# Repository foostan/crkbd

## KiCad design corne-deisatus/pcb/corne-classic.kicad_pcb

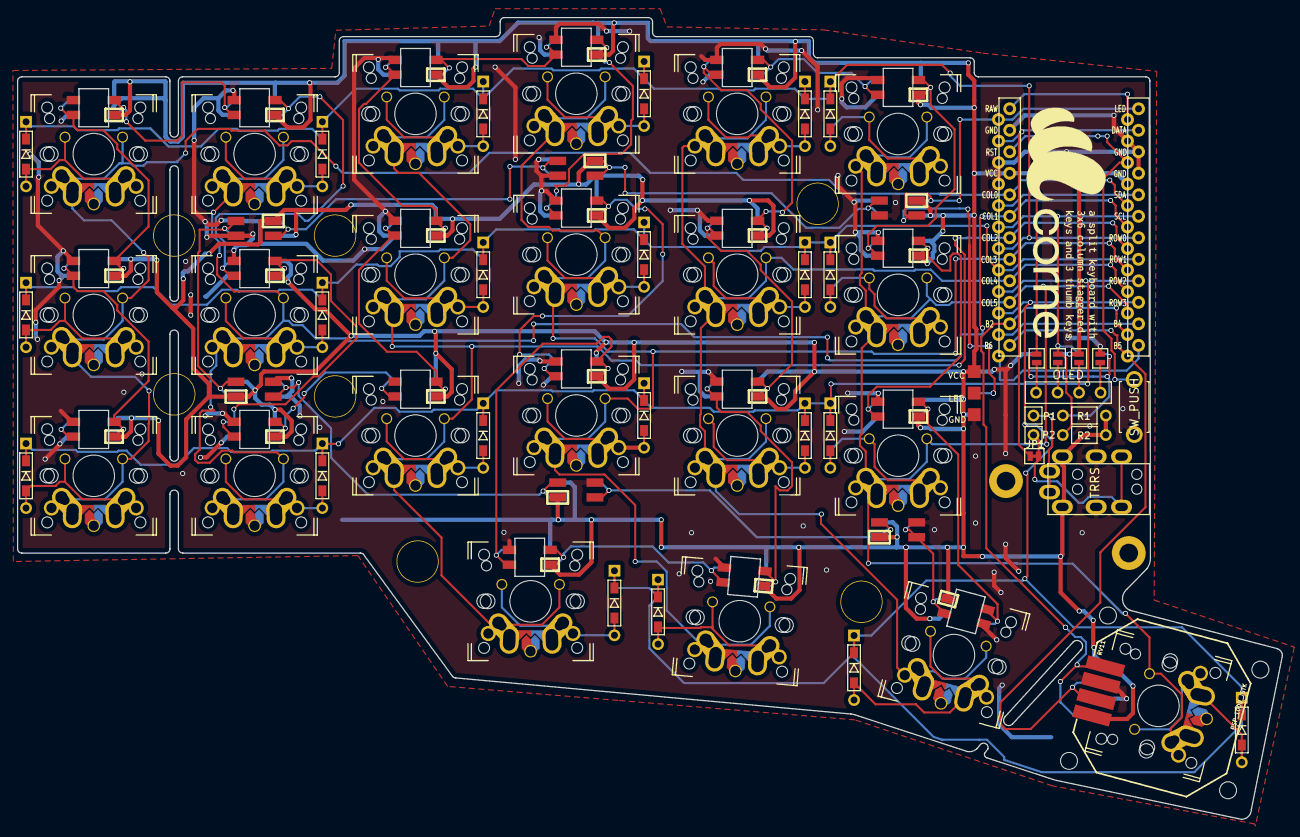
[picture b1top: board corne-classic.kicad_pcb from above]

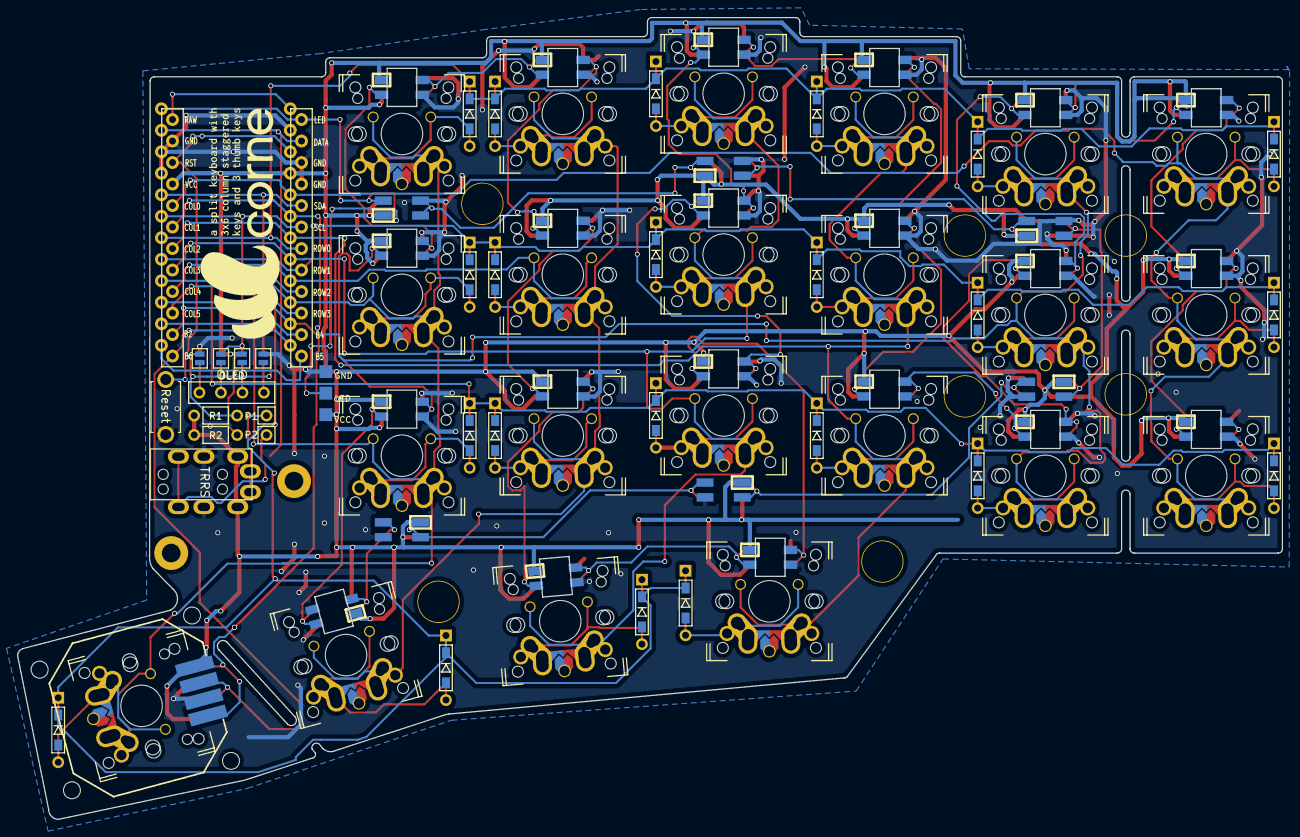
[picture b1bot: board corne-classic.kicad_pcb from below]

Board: 2 copper layers, 149.4 x 94.7 mm, 90 parts (4 on the bottom side), 73 nets.

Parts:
D1, D2, D3, D4, D5, D6, D7, D8, D9, D10, D11, D12, D13, D14, D15, D16, D17, D18, D19, D20, D21, D22: D; D3_TH_SMD
J1: MJ-4PP-9
J2: OLED
J3: LED; StripLED_rev
JP1: JP
JP2, JP3, JP4, JP5, JP6, JP7, JP8, JP9: Jumper
L1, L2, L3, L4, L5, L6: SK6812MINI; SK6812MINI_underglow_rev
L7, L8, L9, L10, L11, L12, L13, L14, L15, L16, L17, L18, L19, L20, L21, L22, L23, L24, L25, L26, L27: SK6812MINI; SK6812MINI_rev
P1, P2: i2c-pin; 1pin_conn
R1, R2: R
RSW1: SW_PUSH; ResetSW
RV11: PSP_1000_JSTK; JOYSTICK-PSP1000-reverse
SW1, SW2, SW3, SW4, SW5, SW6, SW7, SW8, SW9, SW10, SW11, SW12, SW13, SW14, SW15, SW16, SW17, SW18, SW19, SW22: SW_PUSH; MX-ALPS-Choc-X-straight-crane2
SW20, SW21: SW_PUSH; MX-ALPS-Choc-X-straight-crane2-u1.5
U1: ProMicro; ProMicro_v2

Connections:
GND: J1.C, J3.1, JP2.1, JP9.1, L1.2, L2.2, L3.2, L4.2, L5.2, L6.2, L7.2, L8.2, L9.2, L10.2, L11.2, L12.2, L13.2, L14.2, L15.2, L16.2, L17.2, L18.2, L19.2, L20.2, L21.2, L22.2, L23.2, L24.2, L25.2, L26.2, L27.2, RSW1.2, RV11.2, U1.3, U1.4, U1.23
LED: J3.2, L3.3, U1.1
unnamed: D1.2, SW1.2
unnamed: D2.2, SW2.2
unnamed: D3.2, SW3.2
unnamed: D4.2, SW4.2
unnamed: D5.2, SW5.2
unnamed: D6.2, SW6.2
unnamed: D7.2, SW7.2
unnamed: D8.2, SW8.2
unnamed: D9.2, SW9.2
unnamed: D10.2, SW10.2
unnamed: D11.2, SW11.2
unnamed: D12.2, SW12.2
unnamed: D13.2, SW13.2
unnamed: D14.2, SW14.2
unnamed: D15.2, SW15.2
unnamed: D16.2, SW16.2
unnamed: D17.2, SW17.2
unnamed: D18.2, SW18.2
unnamed: D19.2, SW20.2
unnamed: D20.2, SW21.2
unnamed: D21.2, SW22.2
unnamed: D22.2, SW19.2
unnamed: J1.A, P1.1
unnamed: J1.B, JP1.2, P2.1
unnamed: J2.1, JP5.2, JP9.2
unnamed: J2.2, JP4.2, JP8.2
unnamed: J2.3, JP3.2, JP7.2
unnamed: J2.4, JP2.2, JP6.2
unnamed: L1.1, L4.3
unnamed: L1.3, L2.1
unnamed: L2.3, L3.1
unnamed: L4.1, L5.3
unnamed: L5.1, L6.3
unnamed: L7.3, L8.1
unnamed: L9.3, L10.1
unnamed: L10.3, L16.1
unnamed: L11.1, L17.3
unnamed: L11.3, L12.1
unnamed: L12.3, L18.1
unnamed: L13.1, L19.3
unnamed: L7.1, L13.3
unnamed: L8.3, L14.1
unnamed: L14.3, L20.1
unnamed: L15.1, L21.3
unnamed: L9.1, L15.3
unnamed: L16.3, L22.1
unnamed: L17.1, L23.3
unnamed: L18.3, L24.1
unnamed: L20.3, L21.1
unnamed: L22.3, L25.1
unnamed: L23.1, L26.3
unnamed: L24.3, L27.1
unnamed: L25.3, L26.1
unnamed: L6.1, L27.3
SCL: JP4.1, JP7.1, R2.2, U1.6
SDA: JP5.1, JP6.1, R1.2, U1.5
VCC: J1.D, J3.3, JP3.1, JP8.1, L1.4, L2.4, L3.4, L4.4, L5.4, L6.4, L7.4, L8.4, L9.4, L10.4, L11.4, L12.4, L13.4, L14.4, L15.4, L16.4, L17.4, L18.4, L19.4, L20.4, L21.4, L22.4, L23.4, L24.4, L25.4, L26.4, L27.4, R1.1, R2.1, RV11.4, U1.21
analogX: RV11.1, U1.14
analogY: RV11.3, U1.13
col0: SW1.1, SW7.1, SW13.1, U1.20
col1: SW2.1, SW8.1, SW14.1, U1.19
col2: SW3.1, SW9.1, SW15.1, SW19.1, U1.18
col3: SW4.1, SW10.1, SW16.1, SW20.1, U1.17
col4: SW5.1, SW11.1, SW17.1, SW21.1, U1.16
col5: SW6.1, SW12.1, SW18.1, SW22.1, U1.15
data: JP1.1, U1.2
reset: RSW1.1, U1.22
row0: D1.1, D2.1, D3.1, D4.1, D5.1, D6.1, U1.7
row1: D7.1, D8.1, D9.1, D10.1, D11.1, D12.1, U1.8
row2: D13.1, D14.1, D15.1, D16.1, D17.1, D18.1, U1.9
row3: D19.1, D20.1, D21.1, D22.1, U1.10

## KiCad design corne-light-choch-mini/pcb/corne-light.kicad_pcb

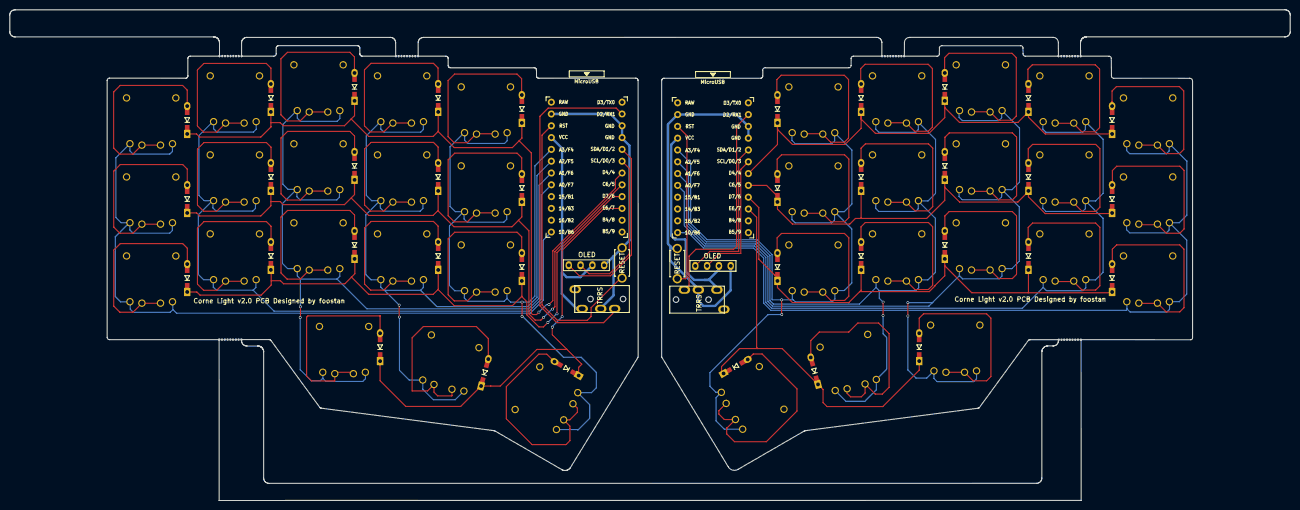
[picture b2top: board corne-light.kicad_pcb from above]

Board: 2 copper layers, 275.5 x 105.6 mm, 80 parts (0 on the bottom side), 66 nets.

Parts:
D2, D3, D4, D5, D6, D8, D9, D10, D11, D12, D14, D15, D16, D17, D18, D19, D20, D21, D23, D24, D25, D26, D27, D29, D30, D31, D32, D33, D35, D36, D37, D38, D39, D40, D41, D42: D; D3_TH
J1, J6: MJ-4PP-9; MJ-4PP-9_1side
J2, J7: OLED; OLED_1side
RSW1, RSW2: SW_PUSH; ResetSW_1side
SW2, SW3, SW4, SW5, SW6, SW8, SW9, SW10, SW11, SW12, SW14, SW15, SW16, SW17, SW18, SW19, SW20, SW21, SW23, SW24, SW25, SW26, SW27, SW29, SW30, SW31, SW32, SW33, SW35, SW36, SW37, SW38, SW39, SW40, SW41, SW42: SW_PUSH; Kailh_PG1232
U1, U2: ProMicro; ProMicro_v3

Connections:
GND: J1.C, J2.4, RSW1.2, U1.3 (GND), U1.4 (GND), U1.23 (GND)
GNDA: J6.C, J7.4, RSW2.2, U2.3 (GND), U2.4 (GND), U2.23 (GND)
unnamed: D2.2 (A), SW2.2
unnamed: D3.2 (A), SW3.2
unnamed: D4.2 (A), SW4.2
unnamed: D5.2 (A), SW5.2
unnamed: D6.2 (A), SW6.2
unnamed: D8.2 (A), SW8.2
unnamed: D9.2 (A), SW9.2
unnamed: D10.2 (A), SW10.2
unnamed: D11.2 (A), SW11.2
unnamed: D12.2 (A), SW12.2
unnamed: D14.2 (A), SW14.2
unnamed: D15.2 (A), SW15.2
unnamed: D16.2 (A), SW16.2
unnamed: D17.2 (A), SW17.2
unnamed: D18.2 (A), SW18.2
unnamed: D19.2 (A), SW19.2
unnamed: D20.2 (A), SW20.2
unnamed: D21.2 (A), SW21.2
unnamed: D23.2 (A), SW23.2
unnamed: D24.2 (A), SW24.2
unnamed: D25.2 (A), SW25.2
unnamed: D26.2 (A), SW26.2
unnamed: D27.2 (A), SW27.2
unnamed: D29.2 (A), SW29.2
unnamed: D30.2 (A), SW30.2
unnamed: D31.2 (A), SW31.2
unnamed: D32.2 (A), SW32.2
unnamed: D33.2 (A), SW33.2
unnamed: D35.2 (A), SW35.2
unnamed: D36.2 (A), SW36.2
unnamed: D37.2 (A), SW37.2
unnamed: D38.2 (A), SW38.2
unnamed: D39.2 (A), SW39.2
unnamed: D40.2 (A), SW40.2
unnamed: D41.2 (A), SW41.2
unnamed: D42.2 (A), SW42.2
SCL: J2.2, U1.6 (3/D0/SCL)
SCL_r: J7.2, U2.6 (3/D0/SCL)
SDA: J2.1, U1.5 (2/D1/SDA)
SDA_r: J7.1, U2.5 (2/D1/SDA)
VCC: J1.D, J2.3, U1.21 (VCC)
VDD: J6.D, J7.3, U2.21 (VCC)
col1: SW2.1, SW8.1, SW14.1, U1.13 (B6/10)
col1_r: SW23.1, SW29.1, SW35.1, U2.13 (B6/10)
col2: SW3.1, SW9.1, SW15.1, U1.17 (F7/A0)
col2_r: SW24.1, SW30.1, SW36.1, U2.17 (F7/A0)
col3: SW4.1, SW10.1, SW16.1, SW19.1, U1.18 (F6/A1)
col3_r: SW25.1, SW31.1, SW37.1, SW40.1, U2.18 (F6/A1)
col4: SW5.1, SW11.1, SW17.1, SW20.1, U1.19 (F5/A2)
col4_r: SW26.1, SW32.1, SW38.1, SW41.1, U2.19 (F5/A2)
col5: SW6.1, SW12.1, SW18.1, SW21.1, U1.20 (F4/A3)
col5_r: SW27.1, SW33.1, SW39.1, SW42.1, U2.20 (F4/A3)
data: J1.B, U1.2 (RX1/D2)
data_r: J6.B, U2.2 (RX1/D2)
reset: RSW1.1, U1.22 (RST)
reset_r: RSW2.1, U2.22 (RST)
row0: D2.1 (K), D3.1 (K), D4.1 (K), D5.1 (K), D6.1 (K), U1.7 (4/D4)
row0_r: D23.1 (K), D24.1 (K), D25.1 (K), D26.1 (K), D27.1 (K), U2.7 (4/D4)
row1: D8.1 (K), D9.1 (K), D10.1 (K), D11.1 (K), D12.1 (K), U1.8 (5/C6)
row1_r: D29.1 (K), D30.1 (K), D31.1 (K), D32.1 (K), D33.1 (K), U2.8 (5/C6)
row2: D14.1 (K), D15.1 (K), D16.1 (K), D17.1 (K), D18.1 (K), U1.9 (6/D7)
row2_r: D35.1 (K), D36.1 (K), D37.1 (K), D38.1 (K), D39.1 (K), U2.9 (6/D7)
row3: D19.1 (K), D20.1 (K), D21.1 (K), U1.10 (7/E6)
row3_r: D40.1 (K), D41.1 (K), D42.1 (K), U2.10 (7/E6)

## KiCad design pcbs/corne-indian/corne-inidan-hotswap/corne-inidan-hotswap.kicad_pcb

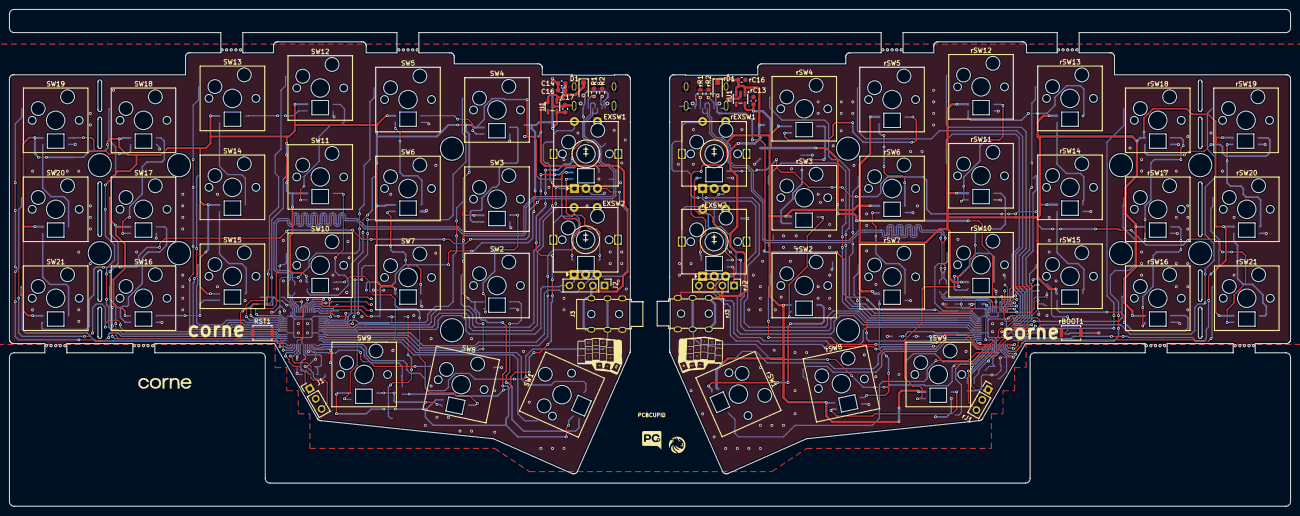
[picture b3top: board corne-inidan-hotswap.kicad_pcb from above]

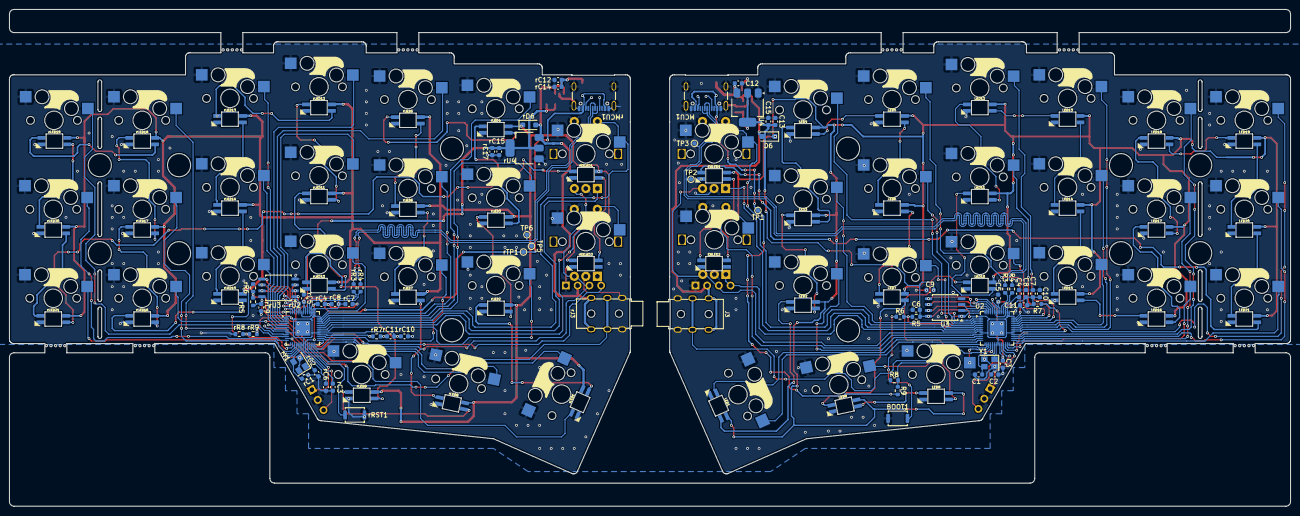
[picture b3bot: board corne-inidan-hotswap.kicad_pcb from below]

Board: 2 copper layers, 277.2 x 107.5 mm, 176 parts (109 on the bottom side), 151 nets.

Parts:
BOOT1: SKRKAGE020; SW_Push_SPST_NO_Alps_SKRK
C1, C2: 20pf; C_0603_1608Metric
C3, C4, C5, C6, C7, C8, C9, C10, C11, C12, C13, C14, C15: 100nf; C_0603_1608Metric
C16, C17: 10uf; C_0603_1608Metric
D1, D6: DSK34; D_SOD-123F
EXLED1, EXLED2: SK6812MINI-E; YS-SK6812MINI-E
EXSW1, EXSW2: RotaryEncoder_Switch; SW_Cherry_MX_1.00u_Hotswap_Rotary-Encoder
J1: Conn_01x03_Pin; PinHeader_1x03_P2.54mm_Vertical
J2: Conn_01x04_Pin; PinHeader_1x04_P2.54mm_Vertical
J3: PJ-3136-B
LED1, LED2, LED3, LED4, LED5, LED6, LED7, LED8, LED9, LED10, LED11, LED12, LED13, LED14, LED15, LED16, LED17, LED18, LED19, LED20, LED21: SK6812MINI-E; YS-SK6812MINI-E
MCU1: USB4105 - Type C USB 2.0 Connector; USB_C_Receptacle_GCT_USB4105-xx-A_16P_TopMnt_Horizontal
R1, R2: 5K1; R_0603_1608Metric
R3, R4: 27R; R_0603_1608Metric
R5, R7, R8: 10K; R_0603_1608Metric
R6: 1K; R_0603_1608Metric
R9: 5K6; R_0603_1608Metric
RST1: SKRKAGE020; SW_Push_SPST_NO_Alps_SKRK
SW1: SW_Push; SW_Cherry_MX_1.50u_Hotswap
SW2, SW3, SW4, SW5, SW6, SW7, SW8, SW9, SW10, SW11, SW12, SW13, SW14, SW15, SW16, SW17, SW18, SW19, SW20, SW21: SW_Push; SW_Cherry_MX_1.00u_Hotswap
TP1, TP2, TP3, TP5, TP6: TestPoint; TestPoint_Pad_D1.0mm
U1: AP2127K-3.3; SOT-23-5
U2: RP2040; QFN-56-1EP_7x7mm_P0.4mm_EP3.2x3.2mm
U3: W25Q32JVSS; SOIC-8_5.3x5.3mm_P1.27mm
U4: AMS1117-3.3; SOT-223-3_TabPin2
Y1: 12Mhz; Crystal_SMD_Abracon_ABM8AIG-4Pin_3.2x2.5mm
rBOOT1: SKRKAGE020; SW_Push_SPST_NO_Alps_SKRK
rC1, rC2: 20pf; C_0603_1608Metric
rC3, rC4, rC5, rC6, rC7, rC8, rC9, rC10, rC11, rC12, rC13, rC14, rC15: 100nf; C_0603_1608Metric
rC16, rC17: 10uf; C_0603_1608Metric
rD1, rD6: DSK34; D_SOD-123F
rEXLED1, rEXLED2: SK6812MINI-E; YS-SK6812MINI-E
rEXSW1, rEXSW2: RotaryEncoder_Switch; SW_Cherry_MX_1.00u_Hotswap_Rotary-Encoder
rJ1: Conn_01x03_Pin; PinHeader_1x03_P2.54mm_Vertical
rJ2: Conn_01x04_Pin; PinHeader_1x04_P2.54mm_Vertical
rJ3: PJ-3136-B
rLED1, rLED2, rLED3, rLED4, rLED5, rLED6, rLED7, rLED8, rLED9, rLED10, rLED11, rLED12, rLED13, rLED14, rLED15, rLED16, rLED17, rLED18, rLED19, rLED20, rLED21: SK6812MINI-E; YS-SK6812MINI-E
rMCU1: USB4105 - Type C USB 2.0 Connector; USB_C_Receptacle_GCT_USB4105-xx-A_16P_TopMnt_Horizontal
rR1, rR2: 5K1; R_0603_1608Metric
rR3, rR4: 27R; R_0603_1608Metric
rR5, rR7, rR8: 10K; R_0603_1608Metric
rR6: 1K; R_0603_1608Metric
rR9: 5K6; R_0603_1608Metric
rRST1: SKRKAGE020; SW_Push_SPST_NO_Alps_SKRK
rSW1: SW_Push; SW_Cherry_MX_1.50u_Hotswap
rSW2, rSW3, rSW4, rSW5, rSW6, rSW7, rSW8, rSW9, rSW10, rSW11, rSW12, rSW13, rSW14, rSW15, rSW16, rSW17, rSW18, rSW19, rSW20, rSW21: SW_Push; SW_Cherry_MX_1.00u_Hotswap
rTP1: TestPoint; TestPoint_Pad_D1.0mm
rU1: AP2127K-3.3; SOT-23-5
rU2: RP2040; QFN-56-1EP_7x7mm_P0.4mm_EP3.2x3.2mm
rU3: W25Q32JVSS; SOIC-8_5.3x5.3mm_P1.27mm
rU4: AMS1117-3.3; SOT-223-3_TabPin2
rY1: 12Mhz; Crystal_SMD_Abracon_ABM8AIG-4Pin_3.2x2.5mm

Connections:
+3.3V: C5.2, C6.2, C7.2, C8.2, C9.2, C10.2, C11.2, C13.2, C15.2, C17.2, R5.1, R7.2, U1.5 (VOUT), U2.1 (IOVDD), U2.10 (IOVDD), U2.22 (IOVDD), U2.33 (IOVDD), U2.42 (IOVDD), U2.43 (ADC_AVDD), U2.44 (VREG_IN), U2.48 (USB_VDD), U2.49 (IOVDD), U3.8 (VCC), U4.2 (VO)
+5V: C12.2, C14.2, C16.2, D1.1 (K), D6.2 (A), J2.2, J3.T, U1.1 (VIN), U1.3 (EN), U4.3 (VI)
/Right/5V_L: rD6.1 (K), rEXLED1.1 (VDD), rEXLED2.1 (VDD), rLED1.1 (VDD), rLED2.1 (VDD), rLED3.1 (VDD), rLED4.1 (VDD), rLED5.1 (VDD), rLED6.1 (VDD), rLED7.1 (VDD), rLED8.1 (VDD), rLED9.1 (VDD), rLED10.1 (VDD), rLED11.1 (VDD), rLED12.1 (VDD), rLED13.1 (VDD), rLED14.1 (VDD), rLED15.1 (VDD), rLED16.1 (VDD), rLED17.1 (VDD), rLED18.1 (VDD), rLED19.1 (VDD), rLED20.1 (VDD), rLED21.1 (VDD)
/Right/BOOT: rBOOT1.1, rR6.2
/Right/D+: rR3.2, rU2.47 (USB_DP)
/Right/D-: rR4.2, rU2.46 (USB_DM)
/Right/KEY_1: rSW1.1, rU2.30 (GPIO19)
/Right/KEY_2: rSW2.1, rU2.34 (GPIO22)
/Right/KEY_3: rSW3.1, rU2.38 (GPIO26_ADC0)
/Right/KEY_4: rSW4.1, rU2.39 (GPIO27_ADC1)
/Right/KEY_5: rSW5.1, rU2.3 (GPIO1)
/Right/KEY_6: rSW6.1, rU2.40 (GPIO28_ADC2)
/Right/KEY_7: rSW7.1, rU2.31 (GPIO20)
/Right/KEY_8: rSW8.1, rU2.28 (GPIO17)
/Right/KEY_9: rSW9.1, rU2.27 (GPIO16)
/Right/KEY_10: rSW10.1, rU2.41 (GPIO29_ADC3)
/Right/KEY_11: rSW11.1, rU2.2 (GPIO0)
/Right/KEY_12: rSW12.1, rU2.4 (GPIO2)
/Right/KEY_13: rSW13.1, rU2.5 (GPIO3)
/Right/KEY_14: rSW14.1, rU2.6 (GPIO4)
/Right/KEY_15: rSW15.1, rU2.7 (GPIO5)
/Right/KEY_16: rSW16.1, rU2.29 (GPIO18)
/Right/KEY_17: rSW17.1, rU2.17 (GPIO14)
/Right/KEY_18: rSW18.1, rU2.12 (GPIO9)
/Right/KEY_19: rSW19.1, rU2.11 (GPIO8)
/Right/KEY_20: rSW20.1, rU2.14 (GPIO11)
/Right/KEY_21: rSW21.1, rU2.18 (GPIO15)
/Right/KEY_EX1: rEXSW1.S2, rU2.37 (GPIO25)
/Right/KEY_EX2: rEXSW2.S2, rU2.35 (GPIO23)
/Right/L_KEY: rLED1.4 (DIN), rU2.13 (GPIO10)
/Right/L_KEY2: rLED1.2 (DOUT), rLED2.4 (DIN)
/Right/L_KEY3: rLED2.2 (DOUT), rLED3.4 (DIN)
/Right/L_KEY4: rLED3.2 (DOUT), rLED4.4 (DIN)
/Right/L_KEY5: rLED4.2 (DOUT), rLED5.4 (DIN)
/Right/L_KEY6: rLED5.2 (DOUT), rLED6.4 (DIN)
/Right/L_KEY7: rLED6.2 (DOUT), rLED7.4 (DIN)
/Right/L_KEY8: rLED7.2 (DOUT), rLED8.4 (DIN)
/Right/L_KEY9: rLED8.2 (DOUT), rLED9.4 (DIN)
/Right/L_KEY10: rLED9.2 (DOUT), rLED10.4 (DIN)
/Right/L_KEY11: rLED10.2 (DOUT), rLED11.4 (DIN)
/Right/L_KEY12: rLED11.2 (DOUT), rLED12.4 (DIN)
/Right/L_KEY13: rLED12.2 (DOUT), rLED13.4 (DIN)
/Right/L_KEY14: rLED13.2 (DOUT), rLED14.4 (DIN)
/Right/L_KEY15: rLED14.2 (DOUT), rLED15.4 (DIN)
/Right/L_KEY16: rLED15.2 (DOUT), rLED16.4 (DIN)
/Right/L_KEY17: rLED16.2 (DOUT), rLED17.4 (DIN)
/Right/L_KEY18: rLED17.2 (DOUT), rLED18.4 (DIN)
/Right/L_KEY19: rLED18.2 (DOUT), rLED19.4 (DIN)
/Right/L_KEY20: rLED19.2 (DOUT), rLED20.4 (DIN)
/Right/L_KEY21: rLED20.2 (DOUT), rLED21.4 (DIN)
/Right/L_KEY22: rEXLED1.4 (DIN), rLED21.2 (DOUT)
/Right/L_KEY23: rEXLED1.2 (DOUT), rEXLED2.4 (DIN)
/Right/RE0A: rEXSW1.A, rU2.36 (GPIO24)
/Right/RE1A: rEXSW2.A, rJ2.4, rU2.8 (GPIO6)
/Right/REB: rEXSW1.B, rEXSW2.B, rJ2.3, rU2.9 (GPIO7)
/Right/RESET: rRST1.1, rU2.26 (RUN)
/Right/SCLK: rU2.52 (QSPI_SCLK), rU3.6 (CLK)
/Right/SD0: rU2.53 (QSPI_SD0), rU3.5 (DI/IO_{0})
/Right/SD1: rU2.55 (QSPI_SD1), rU3.2 (DO/IO_{1})
/Right/SD2: rU2.54 (QSPI_SD2), rU3.3 (~WP/IO_{2})
/Right/SD3: rU2.51 (QSPI_SD3), rU3.7 (~HOLD/~RESET/IO_{3})
/Right/SS: rR5.2, rR6.1, rU2.56 (QSPI_SS), rU3.1 (~CS)
/Right/SWCLK: rJ1.3, rU2.24 (SWCLK)
/Right/SWDIO: rJ1.1, rU2.25 (SWD)
/Right/TX: rJ3.R, rU2.15 (GPIO12)
/Right/USB_VBUS_PIN: rR8.2, rR9.1, rU2.16 (GPIO13)
/Right/U_+: TP6.1, rMCU1.A6 (D+), rMCU1.B6 (D+), rR3.1
/Right/U_-: TP5.1, rMCU1.A7 (D-), rMCU1.B7 (D-), rR4.1
/left/5V_L: D6.1 (K), EXLED1.1 (VDD), EXLED2.1 (VDD), LED1.1 (VDD), LED2.1 (VDD), LED3.1 (VDD), LED4.1 (VDD), LED5.1 (VDD), LED6.1 (VDD), LED7.1 (VDD), LED8.1 (VDD), LED9.1 (VDD), LED10.1 (VDD), LED11.1 (VDD), LED12.1 (VDD), LED13.1 (VDD), LED14.1 (VDD), LED15.1 (VDD), LED16.1 (VDD), LED17.1 (VDD), LED18.1 (VDD), LED19.1 (VDD), LED20.1 (VDD), LED21.1 (VDD)
/left/BOOT: BOOT1.1, R6.2
/left/D+: R3.2, U2.47 (USB_DP)
/left/D-: R4.2, U2.46 (USB_DM)
/left/KEY_1: SW1.1, U2.14 (GPIO11)
/left/KEY_2: SW2.1, U2.12 (GPIO9)
/left/KEY_3: SW3.1, U2.4 (GPIO2)
/left/KEY_4: SW4.1, U2.2 (GPIO0)
/left/KEY_5: SW5.1, U2.41 (GPIO29_ADC3)
/left/KEY_6: SW6.1, U2.3 (GPIO1)
/left/KEY_7: SW7.1, U2.5 (GPIO3)
/left/KEY_8: SW8.1, U2.18 (GPIO15)
/left/KEY_9: SW9.1, U2.17 (GPIO14)
/left/KEY_10: SW10.1, U2.40 (GPIO28_ADC2)
/left/KEY_11: SW11.1, U2.39 (GPIO27_ADC1)
/left/KEY_12: SW12.1, U2.38 (GPIO26_ADC0)
/left/KEY_13: SW13.1, U2.35 (GPIO23)
/left/KEY_14: SW14.1, U2.36 (GPIO24)
/left/KEY_15: SW15.1, U2.37 (GPIO25)
/left/KEY_16: SW16.1, U2.27 (GPIO16)
/left/KEY_17: SW17.1, U2.29 (GPIO18)
/left/KEY_18: SW18.1, U2.31 (GPIO20)
/left/KEY_19: SW19.1, U2.34 (GPIO22)
/left/KEY_20: SW20.1, U2.30 (GPIO19)
/left/KEY_21: SW21.1, U2.28 (GPIO17)
/left/KEY_EX1: EXSW1.S2, U2.6 (GPIO4)
/left/KEY_EX2: EXSW2.S2, U2.11 (GPIO8)
/left/L_KEY: LED1.4 (DIN), U2.13 (GPIO10)
/left/L_KEY2: LED1.2 (DOUT), LED2.4 (DIN)
/left/L_KEY3: LED2.2 (DOUT), LED3.4 (DIN)
/left/L_KEY4: LED3.2 (DOUT), LED4.4 (DIN)
/left/L_KEY5: LED4.2 (DOUT), LED5.4 (DIN)
/left/L_KEY6: LED5.2 (DOUT), LED6.4 (DIN)
/left/L_KEY7: LED6.2 (DOUT), LED7.4 (DIN)
/left/L_KEY8: LED7.2 (DOUT), LED8.4 (DIN)
/left/L_KEY9: LED8.2 (DOUT), LED9.4 (DIN)
/left/L_KEY10: LED9.2 (DOUT), LED10.4 (DIN)
/left/L_KEY11: LED10.2 (DOUT), LED11.4 (DIN)
/left/L_KEY12: LED11.2 (DOUT), LED12.4 (DIN)
/left/L_KEY13: LED12.2 (DOUT), LED13.4 (DIN)
/left/L_KEY14: LED13.2 (DOUT), LED14.4 (DIN)
/left/L_KEY15: LED14.2 (DOUT), LED15.4 (DIN)
/left/L_KEY16: LED15.2 (DOUT), LED16.4 (DIN)
/left/L_KEY17: LED16.2 (DOUT), LED17.4 (DIN)
/left/L_KEY18: LED17.2 (DOUT), LED18.4 (DIN)
/left/L_KEY19: LED18.2 (DOUT), LED19.4 (DIN)
/left/L_KEY20: LED19.2 (DOUT), LED20.4 (DIN)
/left/L_KEY21: LED20.2 (DOUT), LED21.4 (DIN)
/left/L_KEY22: EXLED1.4 (DIN), LED21.2 (DOUT)
/left/L_KEY23: EXLED1.2 (DOUT), EXLED2.4 (DIN)
/left/RE0A: EXSW1.A, U2.7 (GPIO5)
/left/RE1A: EXSW2.A, J2.4, U2.8 (GPIO6)
/left/REB: EXSW1.B, EXSW2.B, J2.3, U2.9 (GPIO7)
/left/RESET: RST1.1, U2.26 (RUN)
/left/SCLK: U2.52 (QSPI_SCLK), U3.6 (CLK)
/left/SD0: U2.53 (QSPI_SD0), U3.5 (DI/IO_{0})
/left/SD1: U2.55 (QSPI_SD1), U3.2 (DO/IO_{1})
/left/SD2: U2.54 (QSPI_SD2), U3.3 (~WP/IO_{2})
/left/SD3: U2.51 (QSPI_SD3), U3.7 (~HOLD/~RESET/IO_{3})
/left/SS: R5.2, R6.1, U2.56 (QSPI_SS), U3.1 (~CS)
/left/SWCLK: J1.3, U2.24 (SWCLK)
/left/SWDIO: J1.1, U2.25 (SWD)
/left/TX: J3.R, U2.15 (GPIO12)
/left/USB_VBUS_PIN: R8.2, R9.1, U2.16 (GPIO13)
/left/U_+: MCU1.A6 (D+), MCU1.B6 (D+), R3.1, TP3.1
/left/U_-: MCU1.A7 (D-), MCU1.B7 (D-), R4.1, TP2.1
GND: BOOT1.2, C1.1, C2.1, C3.1, C4.1, C5.1, C6.1, C7.1, C8.1, C9.1, C10.1, C11.1, C12.1, C13.1, C14.1, C15.1, C16.1, C17.1, EXLED1.3 (VSS), EXLED2.3 (VSS), EXSW1.C, EXSW1.S1, EXSW2.C, EXSW2.S1, J1.2, J2.1, J3.S, LED1.3 (VSS), LED2.3 (VSS), LED3.3 (VSS), LED4.3 (VSS), LED5.3 (VSS), LED6.3 (VSS), LED7.3 (VSS), LED8.3 (VSS), LED9.3 (VSS), LED10.3 (VSS), LED11.3 (VSS), LED12.3 (VSS), LED13.3 (VSS), LED14.3 (VSS), LED15.3 (VSS), LED16.3 (VSS), LED17.3 (VSS), LED18.3 (VSS), LED19.3 (VSS), LED20.3 (VSS), LED21.3 (VSS), MCU1.A1 (GND), MCU1.A12 (GND), MCU1.B1 (GND), MCU1.B12 (GND), MCU1.S1 (SHIELD), R1.2, R2.2, R8.1, RST1.2, SW1.2, SW2.2, SW3.2, SW4.2, SW5.2, SW6.2, SW7.2, SW8.2, SW9.2, SW10.2, SW11.2, SW12.2, SW13.2, SW14.2, SW15.2, SW16.2, SW17.2, SW18.2, SW19.2, SW20.2, SW21.2, U1.2 (GND), U2.19 (TESTEN), U2.57 (GND), U3.4 (GND), U4.1 (GND), Y1.2, Y1.4, rBOOT1.2, rC1.1, rC2.1, rC3.1, rC4.1, rC5.1, rC6.1, rC7.1, rC8.1, rC9.1, rC10.1, rC11.1, rC12.1, rC13.1, rC14.1, rC15.1, rC16.1, rC17.1, rEXLED1.3 (VSS), rEXLED2.3 (VSS), rEXSW1.C, rEXSW1.S1, rEXSW2.C, rEXSW2.S1, rJ1.2, rJ2.1, rJ3.S, rLED1.3 (VSS), rLED2.3 (VSS), rLED3.3 (VSS), rLED4.3 (VSS), rLED5.3 (VSS), rLED6.3 (VSS), rLED7.3 (VSS), rLED8.3 (VSS), rLED9.3 (VSS), rLED10.3 (VSS), rLED11.3 (VSS), rLED12.3 (VSS), rLED13.3 (VSS), rLED14.3 (VSS), rLED15.3 (VSS), rLED16.3 (VSS), rLED17.3 (VSS), rLED18.3 (VSS), rLED19.3 (VSS), rLED20.3 (VSS), rLED21.3 (VSS), rMCU1.A1 (GND), rMCU1.A12 (GND), rMCU1.B1 (GND), rMCU1.B12 (GND), rMCU1.S1 (SHIELD), rR1.2, rR2.2, rR7.2, rR8.1, rRST1.2, rSW1.2, rSW2.2, rSW3.2, rSW4.2, rSW5.2, rSW6.2, rSW7.2, rSW8.2, rSW9.2, rSW10.2, rSW11.2, rSW12.2, rSW13.2, rSW14.2, rSW15.2, rSW16.2, rSW17.2, rSW18.2, rSW19.2, rSW20.2, rSW21.2, rU1.2 (GND), rU2.19 (TESTEN), rU2.57 (GND), rU3.4 (GND), rU4.1 (GND), rY1.2, rY1.4
unnamed: MCU1.A5 (CC1), R1.1
unnamed: MCU1.B5 (CC2), R2.1
unnamed: R7.1, U2.32 (GPIO21)
unnamed: C3.2, C4.2, U2.23 (DVDD), U2.45 (VREG_VOUT), U2.50 (DVDD)
unnamed: C1.2, U2.20 (XIN), Y1.3
unnamed: C2.2, U2.21 (XOUT), Y1.1
unnamed: rMCU1.A5 (CC1), rR1.1
unnamed: rMCU1.B5 (CC2), rR2.1
unnamed: rR7.1, rU2.32 (GPIO21)
unnamed: rC3.2, rC4.2, rU2.23 (DVDD), rU2.45 (VREG_VOUT), rU2.50 (DVDD)
unnamed: rC1.2, rU2.20 (XIN), rY1.3
unnamed: rC2.2, rU2.21 (XOUT), rY1.1
VBUS: D1.2 (A), MCU1.A4 (VBUS), MCU1.A9 (VBUS), MCU1.B4 (VBUS), MCU1.B9 (VBUS), R9.2, TP1.1
r+3.3V: rC5.2, rC6.2, rC7.2, rC8.2, rC9.2, rC10.2, rC11.2, rC13.2, rC15.2, rC17.2, rR5.1, rU1.5 (VOUT), rU2.1 (IOVDD), rU2.10 (IOVDD), rU2.22 (IOVDD), rU2.33 (IOVDD), rU2.42 (IOVDD), rU2.43 (ADC_AVDD), rU2.44 (VREG_IN), rU2.48 (USB_VDD), rU2.49 (IOVDD), rU3.8 (VCC), rU4.2 (VO)
r+5V: rC12.2, rC14.2, rC16.2, rD1.1 (K), rD6.2 (A), rJ2.2, rJ3.T, rU1.1 (VIN), rU1.3 (EN), rU4.3 (VI)
rVBUS: rD1.2 (A), rMCU1.A4 (VBUS), rMCU1.A9 (VBUS), rMCU1.B4 (VBUS), rMCU1.B9 (VBUS), rR9.2, rTP1.1
